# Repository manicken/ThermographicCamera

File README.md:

# Teensy 4.0
Teensy 4.0 Thermal Camera using MLX90640 + ST7789(240x240)/ILI9341(320x240+touch) display

Using Gauss smooting + biqubic interpolation

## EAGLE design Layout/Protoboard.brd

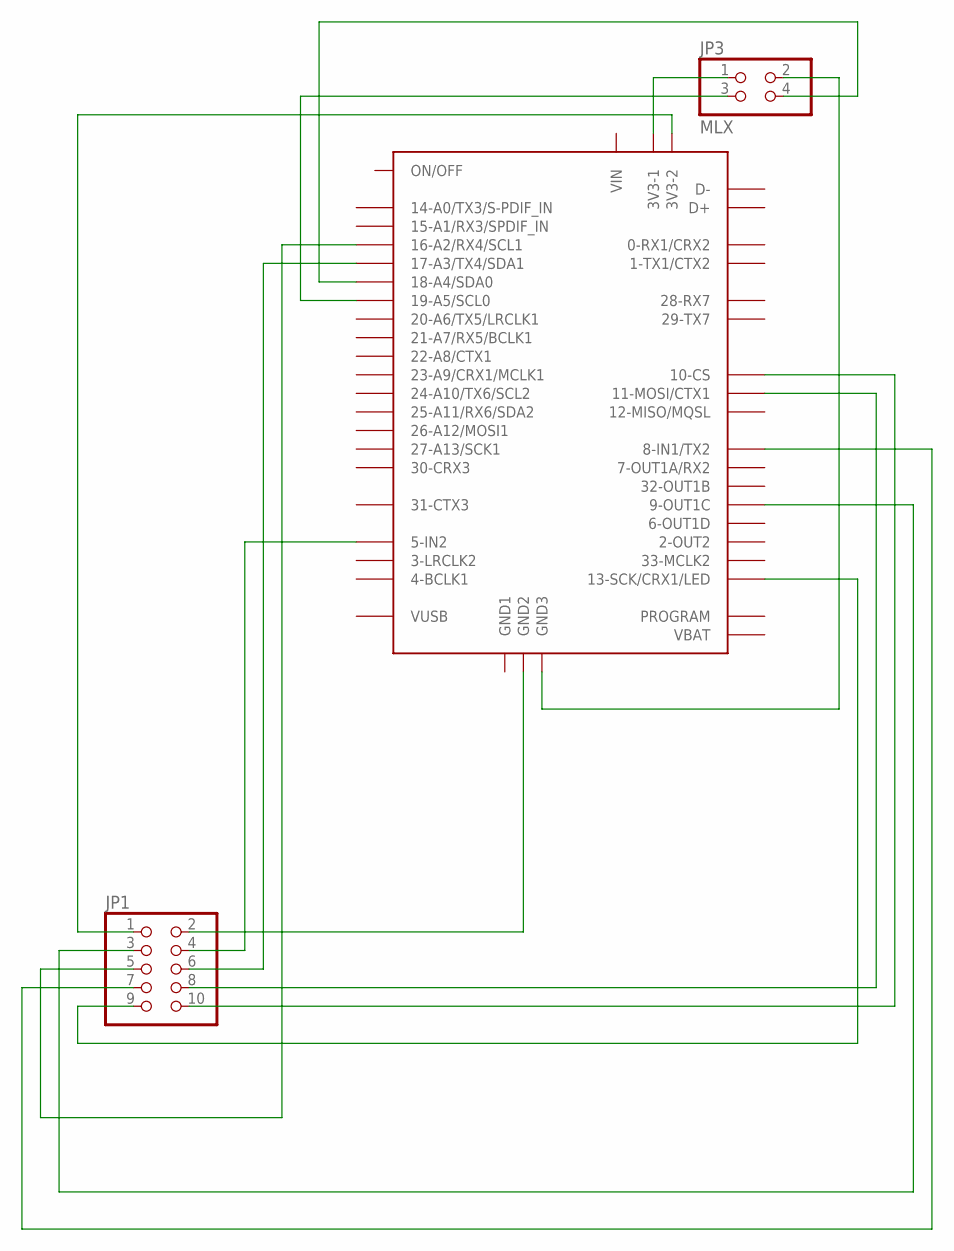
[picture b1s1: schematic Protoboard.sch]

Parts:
JP1: PINHD-2X5; 2X05
JP3: MLX; 2X02
U$1: TEENSY40

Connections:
unnamed: JP1.2, U$1.GND2
unnamed: JP1.1, U$1.3V3-2
unnamed: JP3.1, U$1.3V3-1
unnamed: JP1.9, U$1.13-SCK/CRX1/LED
unnamed: JP3.2, U$1.GND3
unnamed: JP1.7, U$1.8-TX2/IN1 (8-IN1/TX2)
unnamed: JP1.5, U$1.16-A2/RX4/SCL1
unnamed: JP1.6, U$1.17-A3/TX4/SDA1
unnamed: JP1.4, U$1.5-IN2
unnamed: JP1.8, U$1.11-MOSI/CTX1
unnamed: JP1.10, U$1.10-CS/MQSR (10-CS)
unnamed: JP3.4, U$1.18-A4/SDA0
unnamed: JP3.3, U$1.19-A5/SCL0
unnamed: JP1.3, U$1.9-OUT1C

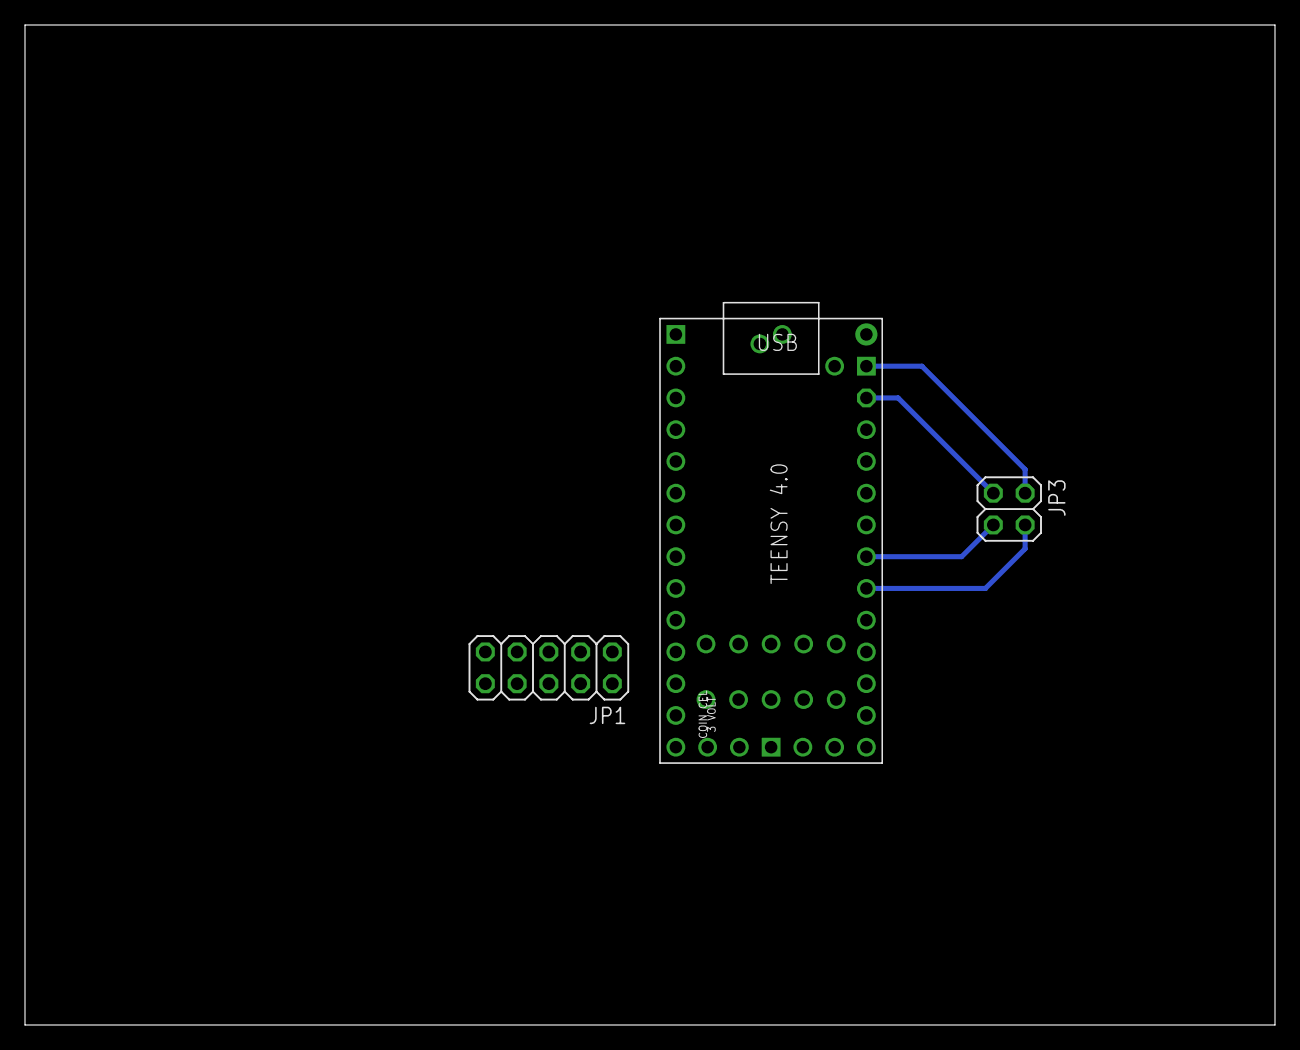
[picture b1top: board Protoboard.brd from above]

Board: 2 copper layers, 100.0 x 80.0 mm, 3 parts (0 on the bottom side), 14 nets.

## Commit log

2022-03-25 combined MLX and TFT examples
2022-03-25 first functional thermal camera MLX+TFT
2022-03-25 implemented Adafruit biqubic interpolation (7fps)
2022-03-29 draft for 'base color'-based color map generation
2022-03-31 add draft PaletteEditor
2022-03-31 some +tests
2022-03-31 drawFromKeyColors nearly finished
2022-03-31 drawFromKeyColors now fully working
2022-03-31 keyProcents now hav the actual step in procent ex (0 25 50 75 100)
2022-04-01 included all color schemes into the PaletteEditor from https://github.com/maxritter/DIY-Thermocam/blob/master/Firmware_V3/src/general/colorschemes.cpp
2022-04-01 included License
2022-04-01 Add SavedSceme pictures generated from Reference_ColorSchemes + converted some to Gradient Palettes
2022-04-01 All Reference ColorSchemes converted into GradientPalettes
2022-04-01 add printAllGradientPalettes function
2022-04-02 try to translate javascript structures to c++
2022-04-02 c++ GradientPalettes structure is decided + all data
2022-04-02 all GP_Data colors is now in decimal form
2022-04-02 all current available GradientPalettes data + def now done
2022-04-03 First version using runtime generated GradientPalettes
2022-04-03 made GradientPalettes.h more clean, so only GP_Def and GP_Data is there
2022-04-05 structured code + usage of SerialCommands lib + USB streaming mode
2022-04-07 better code structure
2022-04-07 code cleanup, move stuff away from main.cpp
2022-04-07 SerialRemoteControl SerialCommands wrapper, base structure done
2022-04-07 Everything have it's own place
2022-04-10 add average functionality for lower noise
2022-04-12 add support for ILI9341 as well
2022-04-12 some fixes + custom fast loop
2022-04-12 some small optimations
2022-04-12 gauss blur + upscale + downscale(removes noise) + upscale final
2022-04-13 draft for multitasking of mlx read and interpolation routine
2022-04-13 draft for multitasking of mlx read and interpolation task
2022-04-14 try to use threading with mlx i2c send but, don't work
2022-04-19 multitasking works but are slower
2022-04-19 static uint16_t mlx90640Frame[834]; // static makes the multithreading switching much faster
2022-04-19 fixed some bugs
2022-04-19 fix Thermal camera init
2022-04-19 some fixes
2022-04-21 USB streaming now prints framenumber so framedrop can be counted
2022-04-21 changed imgM_frame to frame + txtMinT don't begin with .+n
2022-04-21 print fps now only prints to target
2022-04-21 add display enable/disable + images
2022-04-23 First upload
2022-04-24 Update Images
2022-04-28 add average functionality to reduce noise
2022-04-28 add set mlx update rate serial command
2022-04-28 add usb streaming pixelated mode
2022-05-02 USB stream pixelate function now uses better (to understand) formula, + fixes
2022-05-03 add global defines TFT main draw offsets + fixed offset for pixelated mode
2022-05-03 Add MIT app inventor project
